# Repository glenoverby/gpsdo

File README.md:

# gpsdo
A GPS Disciplined Oscillator Controller

**There is a newer version of this project in my 'gpsdo3' repository.**

This is a microcontroller based GPS disciplined oscillator.

The purpose of this device is to synchronize a 10MHz voltage controlled
oscillator with the timing signal from a GPS receiver such that the oscillator
operates at exactly 10mhz.

The process is similar to using a phase-locked loop (PLL) but without the
analog components of a PLL.  The details, however, are not so simple.

The PCB design is version 2, which I have not constructed yet.
Version 1 requires many changes to make it work.

The software directory contains several progams:

* Freq-Find  uses a binary search algorithm to search for a target
frequency.  The program searches for 10,000,000 hz, 9,999,999 hz, and
10,000,001 hz.  The PWM values from this program are used to calculate
the PID constants used in the main control program.

* measure, A program that measures the clock frequency at several PWM settings.

* gpsdo-p, Proportional controller which disciplines an oscillator.
I don't use this version anymore.

* gpsdo-pid2, PID (Proportional, Integral, Derivitive) controller which
disciplines an oscillator to a GPS. 
This has code for an Isotemp 134-10 OCXO and a FOX-801 VCO. This version is still a work in progress.

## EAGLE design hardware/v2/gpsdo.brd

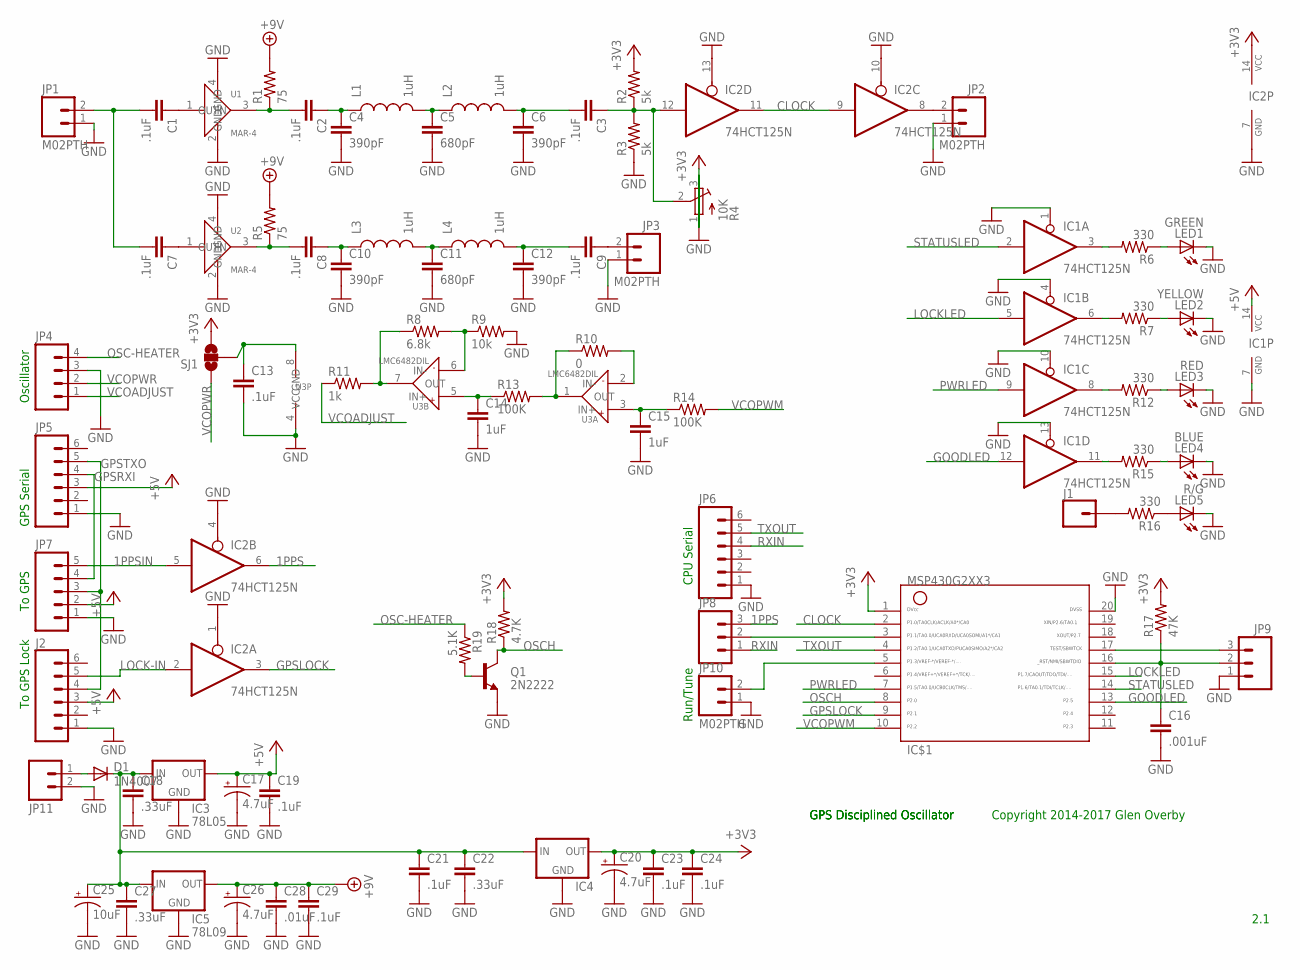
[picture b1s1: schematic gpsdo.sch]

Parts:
C1, C2, C3, C7, C8, C9, C19, C21, C23, C24, C29: .1uF; CAP-PTH-SMALL
C4, C6, C10, C12: 390pF; CAP-PTH-SMALL
C5, C11: 680pF; CAP-PTH-SMALL
C13: .1uF; CAP-PTH-5MM
C14, C15: 1uF; CAP-PTH-SMALL
C16: .001uF; CAP-PTH-SMALL
C17, C20, C26: 4.7uF; EIA3216
C18, C22, C27: .33uF; CAP-PTH-SMALL
C25: 10uF; CPOL-RADIAL-10UF-25V
C28: .01uF; CAP-PTH-SMALL
D1: 1N4007; DIODE-1N4001
IC1, IC2: 74HCT125N; DIL14
IC3: 78L05; TO220-IGO
IC4: 78LXX
IC5: 78L09; 78LXX
IC$1: G2XX3---N20; N20
J1: CONN_01; 1X01
J2: CONN_06SILK_FEMALE_PTH; 1X06
JP1, JP2, JP3, JP10, JP11: M02PTH; 1X02
JP4: M04PTH; 1X04@1
JP5, JP6: M06SILK_FEMALE_PTH; 1X06@1
JP7: M05PTH; 1X05
JP8, JP9: M03PTH; 1X03
L1, L2, L3, L4: 1uH; 1210
LED1: GREEN; LED3MM
LED2: YELLOW; LED3MM
LED3: RED; LED3MM
LED4: BLUE; LED3MM
LED5: R/G; LED3MM
Q1: 2N2222; TO-92
R1, R5: 75; 0207/2V
R2, R3: 5k; 0207/2V
R4: 10K; RTRIM3296W
R6, R7, R12, R15, R16: 330; 0207/2V
R8: 6.8k; 0207/2V
R9: 10k; 0207/2V
R10: 0; 0207/2V
R11: 1k; 0207/2V
R13, R14: 100K; 0207/2V
R17: 47K; 0207/2V
R18: 4.7K; 0207/2V
R19: 5.1K; 0207/2V
SJ1: SOLDERJUMPER_2WAYW; SJ_2W
U1, U2: MAR-4; VV105
U3: LMC6482DIL; DIL08

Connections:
1PPS: IC2.6 (O), JP8.3
1PPSIN: IC2.5 (I), JP7.5
+3V3: C20.A (+), C23.1, C24.1, IC2.14 (VCC), IC4.OUT, IC$1.1, R2.2, R4.1 (A), R17.2, R18.2, SJ1.3
+5V: C17.A (+), C19.1, IC1.14 (VCC), IC3.OUT, J2.3, JP5.3, JP7.2
+9V: C26.A (+), C28.1, C29.1, IC5.OUT, R1.2, R5.2
CLOCK: IC2.9 (I), IC2.11 (O), IC$1.2
GND: C4.2, C5.2, C6.2, C10.2, C11.2, C12.2, C13.2, C14.2, C15.2, C16.2, C17.C (-), C18.2, C19.2, C20.C (-), C21.2, C22.2, C23.2, C24.2, C25.2 (-), C26.C (-), C27.2, C28.2, C29.2, IC1.1 (OE), IC1.4 (OE), IC1.7 (GND), IC1.10 (OE), IC1.13 (OE), IC2.1 (OE), IC2.4 (OE), IC2.7 (GND), IC2.10 (OE), IC2.13 (OE), IC3.GND, IC4.GND, IC5.GND, IC$1.20, J2.1, JP1.1, JP2.1, JP3.1, JP4.3, JP5.1, JP6.1, JP7.1, JP9.1, JP10.1, JP11.2, LED1.K (C), LED2.K (C), LED3.K (C), LED4.K (C), LED5.K (C), Q1.1 (E), R3.1, R4.3 (E), R9.2, U1.2 (GND), U1.4 (GND), U2.2 (GND), U2.4 (GND), U3.4 (GND)
GOODLED: IC1.12 (I), IC$1.13
GPSLOCK: IC2.3 (O), IC$1.9
GPSRXI: JP5.4, JP7.4
GPSTXO: J2.4, JP5.5, JP7.3
LOCK-IN: IC2.2 (I), J2.5
LOCKLED: IC1.5 (I), IC$1.15
unnamed: LED2.A, R7.1
unnamed: C5.1, L1.2, L2.1
unnamed: C3.2, C6.1, L2.2
unnamed: C1.1, U1.1 (IN)
unnamed: C14.1, R13.1, U3.5 (IN+)
unnamed: R10.1, R13.2, U3.1 (OUT)
unnamed: C15.1, R14.1, U3.3 (IN+)
unnamed: IC$1.3, JP8.2
unnamed: C2.2, R1.1, U1.3 (OUT)
unnamed: C3.1, IC2.12 (I), R2.1, R3.2, R4.2 (S)
unnamed: LED1.A, R6.1
unnamed: R8.1, R11.2, U3.7 (OUT)
unnamed: C1.2, C7.2, JP1.2
unnamed: R10.2, U3.2 (IN-)
unnamed: C11.1, L3.2, L4.1
unnamed: D1.A, JP11.1
unnamed: C9.2, C12.1, L4.2
unnamed: IC$1.5, JP10.2
unnamed: IC1.8 (O), R12.2
unnamed: IC1.11 (O), R15.2
unnamed: C8.2, R5.1, U2.3 (OUT)
unnamed: C16.1, IC$1.16, JP9.2, R17.1
unnamed: C8.1, C10.1, L3.1
unnamed: C7.1, U2.1 (IN)
unnamed: C9.1, JP3.2
unnamed: IC$1.17, JP9.3
unnamed: LED5.A, R16.1
unnamed: J1.1, R16.2
unnamed: IC2.8 (O), JP2.2
unnamed: C13.1, SJ1.2, U3.8 (VCC)
unnamed: C2.1, C4.1, L1.1
unnamed: IC1.3 (O), R6.2
unnamed: IC1.6 (O), R7.2
unnamed: R8.2, R9.1, U3.6 (IN-)
unnamed: LED3.A, R12.1
unnamed: LED4.A, R15.1
unnamed: Q1.2 (B), R19.2
OSC-HEATER: JP4.4, R19.1
OSCH: IC$1.8, Q1.3 (C), R18.1
PWRIN: C18.1, C21.1, C22.1, C25.1 (+), C27.1, D1.C, IC3.IN, IC4.IN, IC5.IN
PWRLED: IC1.9 (I), IC$1.7
RXIN: JP6.4, JP8.1
STATUSLED: IC1.2 (I), IC$1.14
TXOUT: IC$1.4, JP6.5
VCOADJUST: JP4.1, R11.1
VCOPWM: IC$1.10, R14.2
VCOPWR: JP4.2, SJ1.1

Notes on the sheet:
To GPS
GPS Serial
Oscillator
CPU Serial
2.1
Run/Tune
To GPS Lock
GPS Disciplined Oscillator
Copyright 2014-2017 Glen Overby

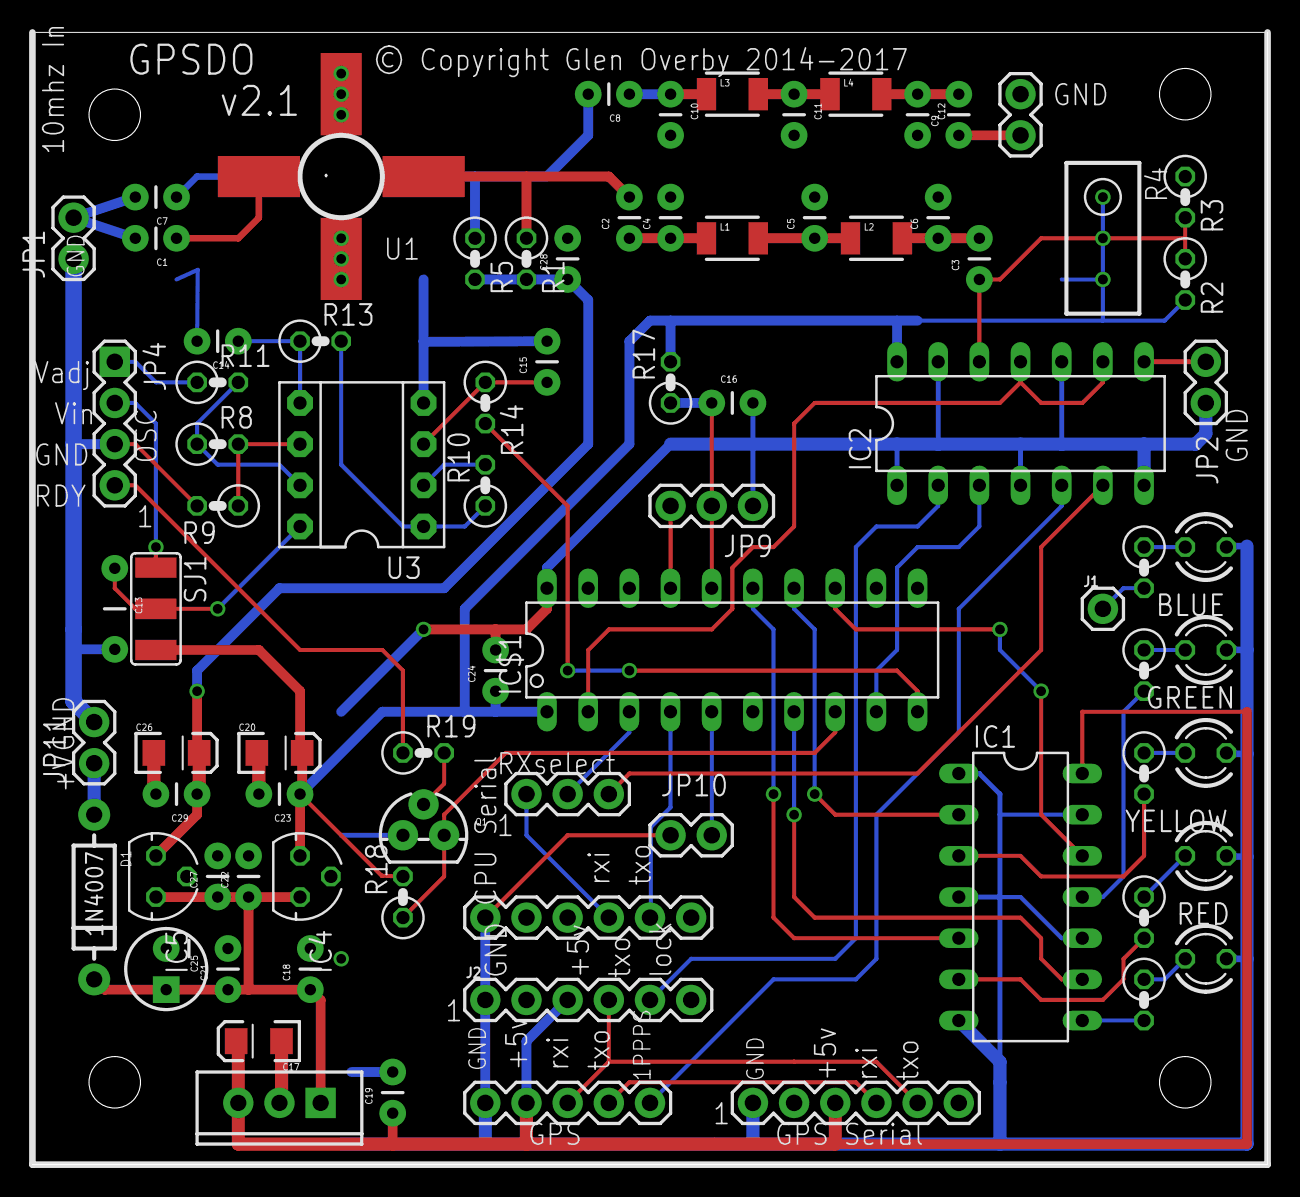
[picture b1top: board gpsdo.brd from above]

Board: 2 copper layers, 76.2 x 69.8 mm, 82 parts (1 on the bottom side), 60 nets.

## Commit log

2017-01-03 Import of documentation and board design.
2017-01-03 Write a new front page
2017-01-03 Fix formatting.
2017-01-04 update schematic.
2017-01-08 tweak formatting.
2017-01-08 Initial software checkin
    This consists of the frequency measurement programs and the first
    generation control code.
2019-06-18 Device description - CSVHFS Paper review version
2019-06-29 Rename components
2019-06-29 Copy in pid2 code
2020-01-15 Replace the description with the CSVHFS 2019 paper
2020-01-15 Current schematic PDF
2024-12-03 CSVHFS paper
2024-12-03 Add a pointer to my GPSDO3 project

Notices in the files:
hardware/v2/gpsdo.brd:
© Copyright Glen Overby 2014-2017
parts and their libraries:
SparkFun-Capacitors: Licensing: Creative Commons ShareAlike 4.0 International - https://creativecommons.org/licenses/by-sa/4.0
